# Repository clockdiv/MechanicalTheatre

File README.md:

# MechanicalTheatre
Control multiple Stepper Motors with Blender Timeline

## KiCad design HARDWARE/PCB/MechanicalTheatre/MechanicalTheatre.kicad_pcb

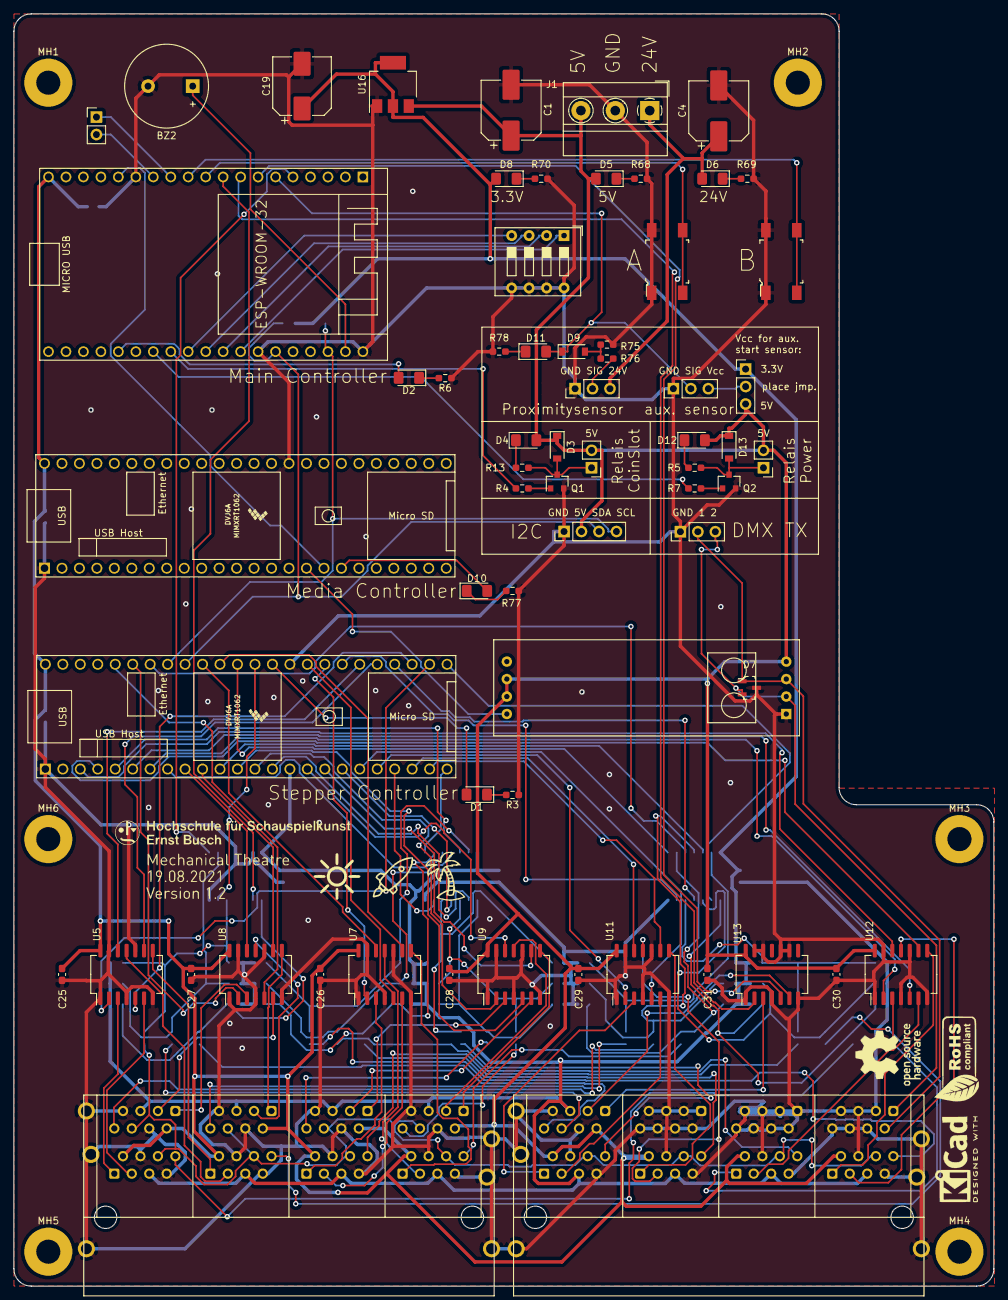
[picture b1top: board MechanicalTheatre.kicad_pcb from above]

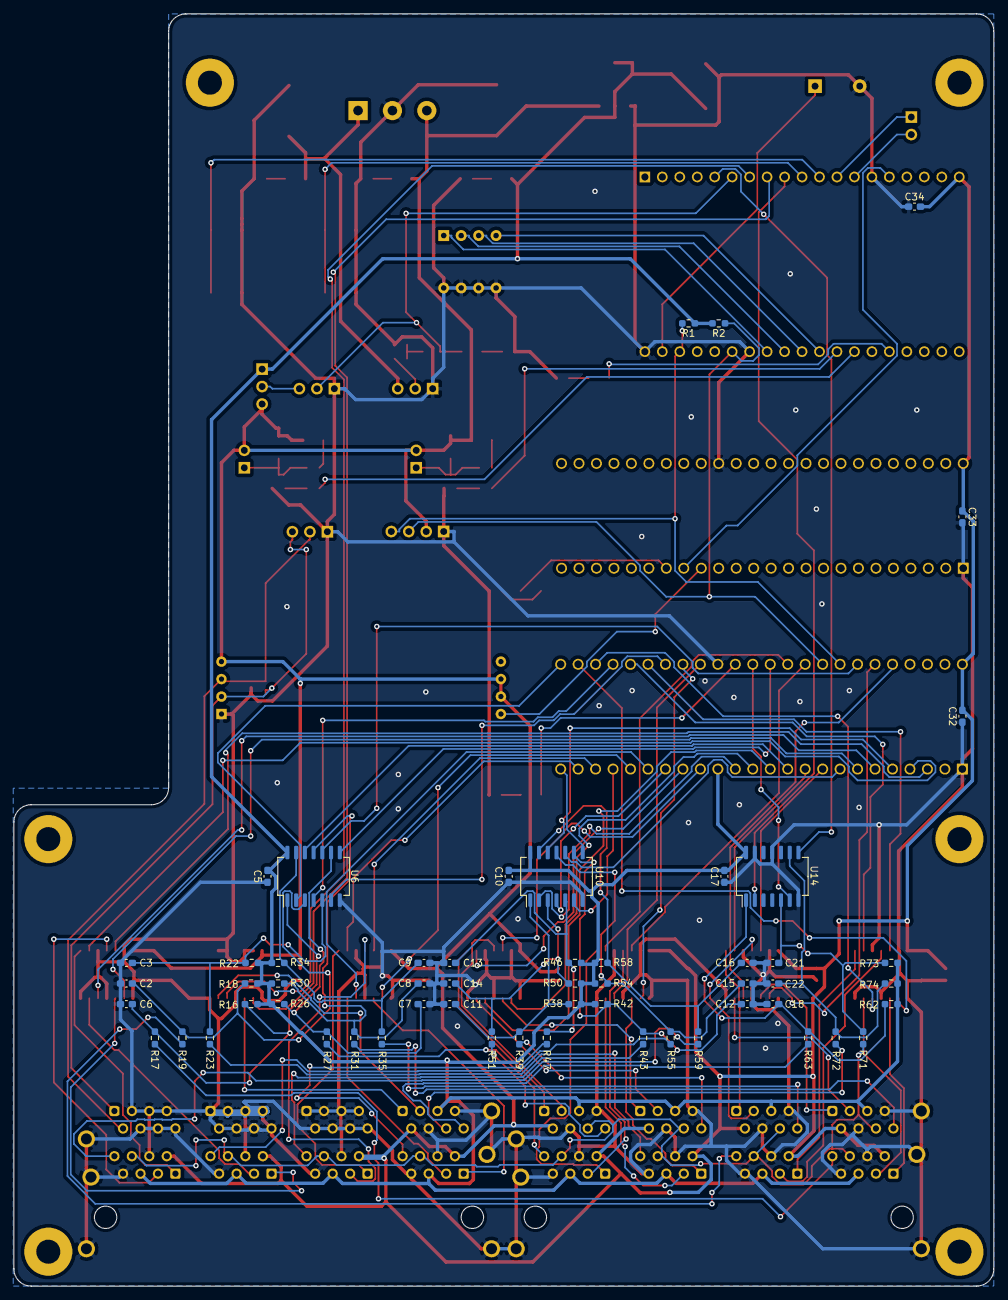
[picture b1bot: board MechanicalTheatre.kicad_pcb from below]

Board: 2 copper layers, 142.5 x 185.0 mm, 128 parts (56 on the bottom side), 138 nets.

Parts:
A1: MAX485-Shield
BZ2: Buzzer; Buzzer_12x9.5RM6.5
C1, C4: 220uF, 35V; CP_Elec_8x10.5
C2, C3, C5, C6, C7, C8, C9, C10, C11, C12, C13, C14, C15, C16, C17, C18, C21, C22, C25, C26, C27, C28, C29, C30, C31, C32, C33, C34: 0.1uF 16V; C_0603_1608Metric_Pad1.08x0.95mm_HandSolder
C19: 100uF, 25V; CP_Elec_8x10
D1, D2, D4, D5, D6, D8, D10, D11, D12: LED; LED_1206_3216Metric_Pad1.42x1.75mm_HandSolder
D3, D9, D13: 1N4148; D_SOD-123
D7: SM712_TCT; SOT-23-3
G1: LOGO; Silkscreen
J1: Power In 5V/24V; TerminalBlock_MetzConnect_Type011_RT05503HBWC_1x03_P5.00mm_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
J2: Conn_01x02_Male_Telefon?; PinHeader_1x02_P2.54mm_Vertical
J3: Conn_E-Magnet; PinHeader_1x02_P2.54mm_Vertical
J4: Conn_PowerRelais; PinHeader_1x02_P2.54mm_Vertical
J5: Conn_01x03_Male_DMX_TX; PinHeader_1x03_P2.54mm_Vertical
J6: Conn_01x03_ExternalSensor; PinHeader_1x03_P2.54mm_Vertical
J8: Conn_01x04_I2C_Display_20x4; PinHeader_1x04_P2.54mm_Vertical
J9: Conn_01x03_ProximitySensor; PinHeader_1x03_P2.54mm_Vertical
J11, J12: RJ45 8x Socket; RJ45_Conrad_8x
JP1: Jumper_3_Open; PinHeader_1x03_P2.54mm_Vertical
MH1, MH2, MH3, MH4, MH5, MH6: MountingHole_3.5mm_Pad
Q1, Q2: BC848; SOT-23
R1, R2, R75: 4.7k; R_0603_1608Metric_Pad0.98x0.95mm_HandSolder
R3, R5, R6, R13, R70, R77, R78: 100; R_0603_1608Metric_Pad0.98x0.95mm_HandSolder
R4, R7, R17, R19, R23, R27, R31, R35, R39, R43, R47, R51, R55, R59, R63, R71, R72: 1k; R_0603_1608Metric_Pad0.98x0.95mm_HandSolder
R16, R18, R22, R26, R30, R34, R38, R42, R46, R50, R54, R58, R62, R73, R74, R76: 10k; R_0603_1608Metric_Pad0.98x0.95mm_HandSolder
R68: 150; R_0603_1608Metric_Pad0.98x0.95mm_HandSolder
R69: 1.2k; R_0603_1608Metric_Pad0.98x0.95mm_HandSolder
S1: Start Show; Switch_Tactile_SMD_6x6mm
S2: Stop Show; Switch_Tactile_SMD_6x6mm
SW1: SW_DIP_x04; SW_DIP_SPSTx04_Slide_9.78x12.34mm_W7.62mm_P2.54mm
U1, U15: Teensy4.1_OuterPins; Teensy41_OuterPinsOnly
U2: ESP32-DEVKITC-32D; MODULE_ESP32-DEVKITC-32D
U5, U7, U8, U9, U11, U12, U13: SN74AHCT125N; SO-14_5.3x10.2mm_P1.27mm
U6, U10, U14: SN74HC14S; SO-14_5.3x10.2mm_P1.27mm
U16: LM1117-3.3; SOT-223-3_TabPin2

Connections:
+3V3: C5.2, C10.2, C17.2, C19.1, D8.2, J11.15, J11.25, J11.35, J11.45, J11.55, J11.65, J11.75, J11.85, J12.15, J12.25, J12.35, J12.45, J12.55, JP1.1, R1.1, R2.2, R16.2, R18.2, R22.2, R26.2, R30.2, R34.2, R38.2, R42.2, R46.2, R50.2, R54.2, R58.2, R62.2, R73.2, R74.2, U1.15, U6.14, U10.14, U14.14, U16.2
+5V: A1.1, A1.6, A1.7, C1.1, C25.2, C26.2, C27.2, C28.2, C29.2, C30.2, C31.2, C32.2, C33.1, C34.2, D3.1, D4.2, D5.2, D12.2, D13.1, J1.3, J3.2, J4.2, J8.2, J11.12, J11.22, J11.32, J11.42, J11.52, J11.62, J11.72, J11.82, J12.12, J12.22, J12.32, J12.42, J12.52, JP1.3, U1.48, U2.19, U5.14, U7.14, U8.14, U9.14, U11.14, U12.14, U13.14, U15.48, U16.3
+24V: C4.1, D6.2, J1.1, J9.3
/DMX_TX: A1.5, U15.16
/GENERAL_END_SWITCH_TEENSY: J11.16, J11.26, J11.36, J11.46, J11.56, J11.66, J11.76, J11.86, J12.16, J12.26, J12.36, J12.46, R71.2
/I2C_SCL: J8.4, R1.2, U1.41, U2.22
/I2C_SDA: J8.3, R2.1, U1.40, U2.25
/PROX_SENSOR: D9.1, D11.2, J6.2, U2.6
/RELAIS_24V+5V: R7.2, U2.32
/RELAIS_E-MAGNET: R4.2, U2.31
/START_STOP_TRIGGER: U2.15, U15.17
/STEPPER_1_DIR: U1.26, U5.2
/STEPPER_1_END: U1.25, U6.2
/STEPPER_1_STEP: U1.27, U5.5
/STEPPER_2_DIR: U1.29, U5.9
/STEPPER_2_END: U1.28, U6.4
/STEPPER_2_STEP: U1.30, U5.12
/STEPPER_3_DIR: U1.32, U7.2
/STEPPER_3_END: U1.31, U6.6
/STEPPER_3_STEP: U1.33, U7.5
/STEPPER_4_DIR: U1.38, U7.9
/STEPPER_4_END: U1.37, U6.8
/STEPPER_4_STEP: U1.39, U7.12
/STEPPER_5_DIR: U1.43, U8.2
/STEPPER_5_END: U1.42, U6.10
/STEPPER_5_STEP: U1.44, U8.5
/STEPPER_6_DIR: U1.10, U8.9
/STEPPER_6_END: U1.11, U6.12
/STEPPER_6_STEP: U1.9, U8.12
/STEPPER_7_DIR: U1.13, U9.2
/STEPPER_7_END: U1.14, U10.2
/STEPPER_7_STEP: U1.12, U9.5
/STEPPER_8_DIR: U1.17, U9.9
/STEPPER_8_END: U1.18, U10.4
/STEPPER_8_STEP: U1.16, U9.12
/STEPPER_9_DIR: U1.20, U11.2
/STEPPER_9_END: U1.21, U10.6
/STEPPER_9_STEP: U1.19, U11.5
/STEPPER_10_DIR: U1.23, U11.9
/STEPPER_10_END: U1.24, U10.8
/STEPPER_10_STEP: U1.22, U11.12
/STEPPER_11_DIR: U1.7, U12.2
/STEPPER_11_END: U1.8, U10.10
/STEPPER_11_STEP: U1.6, U12.5
/STEPPER_12_DIR: U1.4, U12.9
/STEPPER_12_END: U1.5, U10.12
/STEPPER_12_STEP: U1.3, U12.12
/STEPPER_13_DIR: U2.8, U13.2
/STEPPER_13_END: U2.9, U14.2
/STEPPER_13_STEP: U2.7, U13.5
/Stepper Connection 13/END_ALL: J12.56, R72.2
/TEENSY_GENERAL_ENDSWITCH_DEBOUNCED: U1.36, U14.6
GND: A1.4, BZ2.2, C1.2, C2.2, C3.2, C4.2, C5.1, C6.2, C7.2, C8.2, C9.2, C10.1, C11.2, C12.2, C13.2, C14.2, C15.2, C16.2, C17.1, C18.2, C19.2, C21.2, C22.2, C25.1, C26.1, C27.1, C28.1, C29.1, C30.1, C31.1, C32.1, C33.2, C34.1, D7.3, J1.2, J5.1, J6.1, J8.1, J9.1, J11.14, J11.17, J11.24, J11.27, J11.34, J11.37, J11.44, J11.47, J11.54, J11.57, J11.64, J11.67, J11.74, J11.77, J11.84, J11.87, J11.SH, J12.14, J12.17, J12.24, J12.27, J12.34, J12.37, J12.44, J12.47, J12.54, J12.57, J12.61, J12.62, J12.63, J12.64, J12.65, J12.66, J12.67, J12.68, J12.71, J12.72, J12.73, J12.74, J12.75, J12.76, J12.77, J12.78, J12.83, J12.84, J12.85, J12.86, J12.87, J12.88, J12.SH, Q1.2, Q2.2, R3.1, R6.1, R68.2, R69.1, R70.2, R75.1, R77.1, R78.1, S1.1, S1.2, S2.1, S2.2, SW1.5, SW1.6, SW1.7, SW1.8, U1.1, U1.34, U2.14, U2.20, U2.26, U5.1, U5.4, U5.7, U5.10, U5.13, U6.7, U7.1, U7.4, U7.7, U7.10, U7.13, U8.1, U8.4, U8.7, U8.10, U8.13, U9.1, U9.4, U9.7, U9.10, U9.13, U10.7, U11.1, U11.4, U11.7, U11.10, U11.13, U12.1, U12.4, U12.7, U12.10, U12.13, U13.1, U13.4, U13.7, U13.9, U13.10, U13.12, U13.13, U14.7, U14.11, U14.13, U15.1, U15.34, U16.1
unnamed: A1.2, D7.1, J5.2, J12.82
unnamed: A1.3, D7.2, J5.3, J12.81
unnamed: BZ2.1, U2.21
unnamed: C2.1, R18.1, R19.2, U6.3
unnamed: C3.1, R22.1, R23.2, U6.5
unnamed: C6.1, R16.1, R17.2, U6.1
unnamed: C7.1, R26.1, R27.2, U6.9
unnamed: C8.1, R30.1, R31.2, U6.11
unnamed: C9.1, R34.1, R35.2, U6.13
unnamed: C11.1, R38.1, R39.2, U10.1
unnamed: C12.1, R42.1, R43.2, U10.9
unnamed: C13.1, R46.1, R47.2, U10.5
unnamed: C14.1, R50.1, R51.2, U10.3
unnamed: C15.1, R54.1, R55.2, U10.11
unnamed: C16.1, R58.1, R59.2, U10.13
unnamed: C18.1, R62.1, R63.2, U14.1
unnamed: C21.1, R71.1, R73.1, U14.5
unnamed: C22.1, R72.1, R74.1, U14.9
unnamed: D1.1, R3.2
unnamed: D1.2, U1.35
unnamed: D2.1, R6.2
unnamed: D2.2, U2.34
unnamed: D3.2, J3.1, Q1.3, R13.1
unnamed: D4.1, R13.2
unnamed: D5.1, R68.1
unnamed: D6.1, R69.2
unnamed: D8.1, R70.1
unnamed: D9.2, R75.2, R76.1
unnamed: D10.1, R77.2
unnamed: D10.2, U15.18
unnamed: D11.1, R78.2
unnamed: D12.1, R5.2
unnamed: D13.2, J4.1, Q2.3, R5.1
unnamed: J2.1, U2.12
unnamed: J2.2, U2.13
unnamed: J6.3, JP1.2
unnamed: J9.2, R76.2
unnamed: J11.11, U5.3
unnamed: J11.13, U5.6
unnamed: J11.18, R17.1
unnamed: J11.21, U5.8
unnamed: J11.23, U5.11
unnamed: J11.28, R19.1
unnamed: J11.31, U7.3
unnamed: J11.33, U7.6
unnamed: J11.38, R23.1
unnamed: J11.41, U7.8
unnamed: J11.43, U7.11
unnamed: J11.48, R27.1
unnamed: J11.51, U8.3
unnamed: J11.53, U8.6
unnamed: J11.58, R31.1
unnamed: J11.61, U8.8
unnamed: J11.63, U8.11
unnamed: J11.68, R35.1
unnamed: J11.71, U9.3
unnamed: J11.73, U9.6
unnamed: J11.78, R39.1
unnamed: J11.81, U9.8
unnamed: J11.83, U9.11
unnamed: J11.88, R51.1
unnamed: J12.11, U11.3
unnamed: J12.13, U11.6
unnamed: J12.18, R47.1
unnamed: J12.21, U11.8
unnamed: J12.23, U11.11
unnamed: J12.28, R43.1
unnamed: J12.31, U12.3
unnamed: J12.33, U12.6
unnamed: J12.38, R55.1
unnamed: J12.41, U12.8
unnamed: J12.43, U12.11
unnamed: J12.48, R59.1
unnamed: J12.51, U13.3
unnamed: J12.53, U13.6
unnamed: J12.58, R63.1
unnamed: Q1.1, R4.1
unnamed: Q2.1, R7.1
unnamed: S1.3, S1.4, U2.10
unnamed: S2.3, S2.4, U2.11
unnamed: SW1.1, U2.27
unnamed: SW1.2, U2.28
unnamed: SW1.3, U2.29
unnamed: SW1.4, U2.30
unnamed: U2.5, U14.8

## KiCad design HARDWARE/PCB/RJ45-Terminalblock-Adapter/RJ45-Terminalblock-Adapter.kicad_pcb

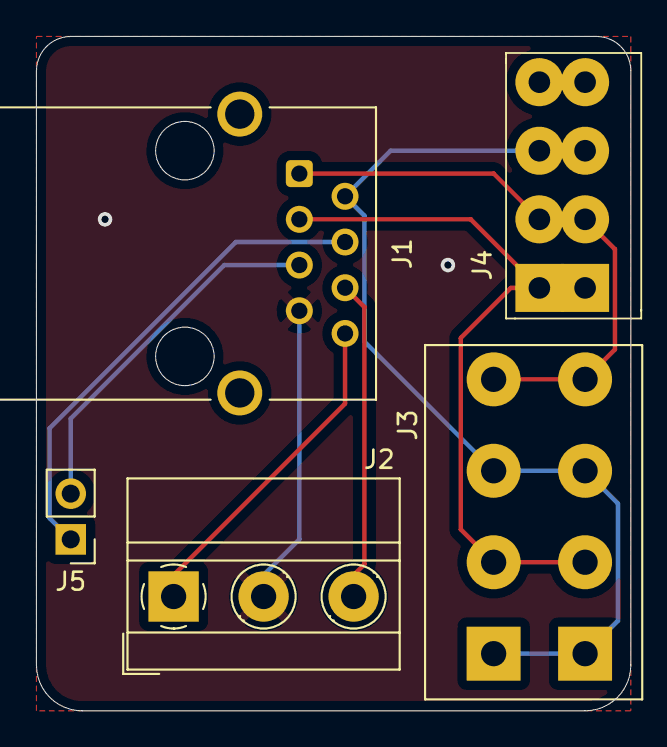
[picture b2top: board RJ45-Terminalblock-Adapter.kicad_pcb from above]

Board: 2 copper layers, 33.0 x 37.5 mm, 5 parts (0 on the bottom side), 8 nets.

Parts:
J1: RJ45; RJ45_Conrad_1586526
J2: Screw_Terminal_01x03; TerminalBlock_MetzConnect_Type011_RT05503HBWC_1x03_P5.00mm_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
J3: Conn_01x04 5.08; Terminalblock_1x4_5.08mm
J4: Conn_01x04 3.81; Terminalblock_1x4_3.81mm
J5: Conn_01x02_Male; PinHeader_1x02_P2.54mm_Vertical

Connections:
/5V: J1.2, J3.1, J3.3, J4.3
/DIR: J1.1, J3.4, J4.2
/END_SW_1: J1.8, J2.1
/END_SW_2: J1.6, J2.3
/GND: J1.7, J2.2
/STEP: J1.3, J3.2, J4.1
unnamed: J1.4, J5.1
unnamed: J1.5, J5.2

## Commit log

2021-06-01 driving multiple steppers
2021-06-03 motor direction invert; end-switch
    - directionInvert added to MotorUnit::initDriver method
    - only basic test for the end-switch, no functional implementation yet
2021-06-03 Init motors at end switches
    added windows-support for serialport list in blender add-on. todo: switch os automatically
2021-06-07 Create ESP32_MainController.ino
    First quick test for the proximity sensor
2021-06-08 Update ESP32_MainController.ino
    state machine, work in progress
2021-06-09 Update ESP32_MainController.ino
    updated pin numbers, minor logic changes
2021-06-11 added minPulseWidth
2021-06-13 KiCad schematic
2021-06-13 untested but necessary code refactoring
    - separate files and namespace for file process code
    - reorganized state machine
2021-06-14 update to esp32_maincontroller
2021-06-14 i2c Communication esp32
    Communication between teensy and esp32
2021-06-14 i2c Communication Teensy
    Communication between Teensy and ESP32
2021-06-14 i2c Communication
2021-07-06 main pcb v1.0
2021-07-06 renaming
2021-07-09 Migration to VSCode #1
    VSCode Project for StepperController
2021-07-09 fixes in kicad file, no actual changes
2021-07-12 teensy: different motor configurations
    added support for 2, 4 and 10 motor units
2021-07-14 minor changes in motor unit
2021-07-14 StateMachine for MotorUnits
    - added debounce lib for endswitches
    - statemachine for motorunits
    - refactoring and cleanup
2021-07-19 VSCode Project for MainController (ESP32)
    Created VSCode Project for MainController
    - MainController and StepperController share most of the code now
2021-07-26 all Motors in MainController
    - added all Motors on MainController
    - relais
    - keyframeProcess uses proper filenames
2021-07-27 i2c communication teensy-esp
    - ESP32 and Teensy are communicating witih each other via i2c. works but needs improvement..
2021-07-29 Communication between Microcontrollers
    - improved i2c
    - triggered communication between esp and second teensy
2021-08-02 LED-Wall Tests
    - Tests with the LED-Wall
2021-08-02 added MediaController
    - MediaController plays Audiofiles and the DMX-Show
    - quadrophonic Audioplayback works
    - basic dmx connection works with teensydmx
2021-08-05 new pcb
    Version 1.1 of pcb
2021-08-18 WiFi and Telegram Support
    added WiFi and Telegram to MainController (esp32)
2021-08-21 motor reset dependencies
2021-08-21 pcb v1.2
    - pcb v1.2 in production.
    - startet to write a manual
2021-08-24 Coinslot sensor added
    - coinslot working, inkl. magnet
    - missing motor-reset-dependencies from last merge added
2021-08-30 Fixed Motor Movement
    - minPulseWidth set to 15us instead of 50us
    - processing-app to visualize the deltaPosition
    - stateMachine added to MediaController
2021-08-30 PCB v1.2
2021-08-30 Hardware Test for PCB v1.2
    - MediaController Start_Stop_Trigger needs to be Pin 27, not 25
2021-09-02 updates on MediaController
2021-09-02 changed MediaController
    - no Interrupt pin, but normal debounced triggerinput
2021-09-03 updates on all
    - StepperController deletes it's files before new upload
    - i2c Handler debug
    - MediaController turns all LEDs off
2021-09-03 StepperController
    - changed stupid timing error
    - changes in configuration12 file
2021-09-03 changes in MediaController
    - fixed stupid timing error
    - added feature to keep power supply always on in maincontroller
2021-09-03 swaped i2c with pin-requests
2021-09-03 Stepper and Media
2021-09-03 Main Controller
2021-09-04 debugging
2021-09-04 stepper + mediacontroller
    - using i2c again for communication
    - mediacontroller still crashing
2021-09-04 debugging in MainController
2021-09-05 stepper controller i2c test
2021-09-05 main controller i2c test function
2021-09-06 Bugfixes
    - memory access error fixed
    - StateToString in MotorUnit (not yet in Main)
2021-09-07 Code refactoring
    - esp32 can send stop signal to teensys
    - stateToString Function in main() on steppercontroller
2021-09-08 added stopsign
2021-09-08 MediaController
    - added fade out on retrigger
2021-09-09 Updates @construction site day 1
    - updated motor-configurations in StepperController
    - temporarly deactivated stop-sign-stepper-motor in MainController
2021-09-10 added Stop-Dependencies for motors
    - Motors watch out for each other, so one connected motor stops when another drives into the endswitch
    - new blender file with movement experiments
2021-09-10 changes in stepper init positions
2021-09-12 Media Controller
    - loads dmx data into extmem (psram)
2021-09-13 Media Controller
    - removed some buffer overflows when uploading huge amount of dmx-data
    - added more dmx-channels for background led wall to the blender-file
2021-09-21 added Feierabend-Timer
    - stops after 14 hours
    - number of played shows is stored in eeprom
2022-07-27 Coinslot Machine added
2025-11-17 added handwritten notes for documentation
2025-11-17 renamed notes
2025-11-17 added files for documentation
